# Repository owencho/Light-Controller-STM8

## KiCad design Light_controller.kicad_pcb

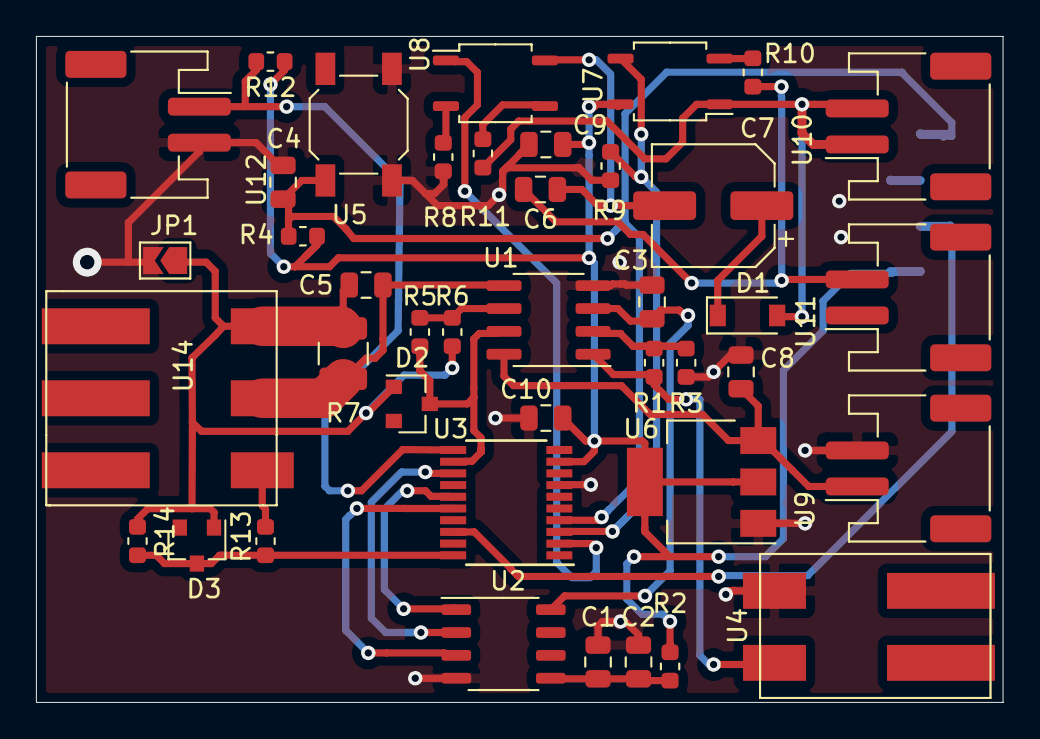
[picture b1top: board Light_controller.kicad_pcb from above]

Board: 2 copper layers, 53.7 x 37.0 mm, 42 parts (1 on the bottom side), 28 nets.

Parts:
C1, C2, C3, C4, C5, C6, C8, C9, C10: C; C_0805_2012Metric
C7: 470uF; CP_Elec_6.3x7.7
D1: 1N5819HW; D_SOD-123
D2, D3: BZX84Cxx; D_SOT-23_ANK
JP1: Jumper_2_Open; SolderJumper-2_P1.3mm_Open_TrianglePad1.0x1.5mm
R1, R2, R3, R4, R5, R6, R8, R9, R10, R12, R13, R14: R; R_0603_1608Metric
R7: 0.01Ω; R_1210_3225Metric
R11: 1K; R_0603_1608Metric
U1: LM358; SOIC-8_3.9x4.9mm_P1.27mm
U2: PT8211-S; SOP-8_3.9x4.9mm_P1.27mm
U3: STM8S003F3P; TSSOP-20_4.4x6.5mm_P0.65mm
U4: SMD_2062; LEDSMD2062
U5: tact_sw; SW_SPST_SKQG_WithStem
U6: AMS1117-5.0; SOT-223-3_TabPin2
U7, U8: EL357N-C; SOP-4_3.8x4.1mm_P2.54mm
U9, U10, U11, U12: PH2.0_horizontal; JST_PH_S2B-PH-SM4-TB_1x02-1MP_P2.00mm_Horizontal
U13: PinSocket_1x4; custom_pinsocket_1x04_p2.54
U14: SMD2063

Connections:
/5V_SUPPLY: C9.2, C10.1, R2.2, R4.1, R12.1, U3.9, U6.2, U7.4, U13.1
/12V_INPUT: C8.1, U1.8, U6.3, U9.1
/C_SENSOR: D2.1, R5.2, U1.7, U3.12
/EXT_GND: C6.2, R10.2, U11.2
/LED+: R13.1, U14.3
/LED-: C5.2, D2.2, D3.2, JP1.1, R6.2, R7.1, R14.2, U14.1
/LED_SENSE: C5.1, R7.2, U1.5, U14.2
/RCH: C3.1, U1.3, U2.8
/RESET: C4.1, R4.2, U3.4, U5.2, U13.4
/RX_in: D1.2, R11.2, U7.1, U10.1, U10.2
/SPI_MOSI: U2.3, U3.16
/SPI_SCK: U2.1, U3.15
/SWIM: U3.18, U13.2
/TEMP_SENSOR: R12.2, U3.11, U12.1
/UART_RX: R9.1, U3.3, U7.3
/UART_TX: U3.2, U8.1
/V_SENSOR: D3.1, R13.2, R14.1, U3.20
/WS: U2.2, U3.13
GND: C1.2, C2.2, C3.2, C4.2, C8.2, C9.1, C10.2, JP1.2, R3.2, R8.1, R9.2, U1.4, U2.4, U3.7, U4.2, U5.1, U6.1, U9.2, U12.2, U13.3
unnamed: C1.1, C2.1, R2.1, U2.5
unnamed: C6.1, C7.2, U8.4
unnamed: C7.1, D1.1
unnamed: R1.1, R3.1, U1.2
unnamed: R1.2, U1.1, U4.1
unnamed: R5.1, R6.1, U1.6
unnamed: R8.2, U8.2
unnamed: R10.1, U7.2
unnamed: R11.1, U8.3

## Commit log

2020-03-08 added digikey library and designed first edition of the schematic for light controller
2020-03-11 added extra circuit for the current sensor
2020-03-21 added all circuit except temperature sensor
2020-03-24 modified ph2.0 to smd , changed thermistor to a ph2.0 and rerouted the layout again with via
2020-03-24 updated newer schematic , havent add the custom footprint and havent change the design layout
2020-03-28 modified layout but havent fill ground yet
2020-04-12 updated the layout
2020-04-12 updated layout
2020-04-24 updated circuit with larger trace on high current
2020-04-28 modified the custom footprint, finalized the schematic and layout of the pcb design for stm8
2020-05-12 updated library location to ensure library is working on another pc
2020-11-23 updated light controller pcb
2020-11-30 added comment for sensor resistor resistance
2020-12-14 added esp32,stm32 circuit
2020-12-16 modified uart circuit for stm8 and stm32
2020-12-17 updated schematic for stm8
2020-12-31 updated schematics for stm8 and esp32
